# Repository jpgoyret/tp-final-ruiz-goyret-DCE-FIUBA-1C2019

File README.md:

# tp-final-ruiz-goyret-DCE-FIUBA-1C2019
Trabajo Práctico final de la materia Diseño de Circuitos Electrónicos en FIUBA - 1°C 2019

Integrantes del grupo:

  * Santiago Ruiz (98052)
  * Juan Pablo Goyret (99081)

## Resumen del trabajo práctico

El trabajo consiste en el diseño, simulación y armado en PCB de un amplificador de audio de potencia mayor a 40W. El tipo de amplificador diseñado es un clase H con etapa de salida en paralelo, realizando la conmutación propia de esta configuración mediante transistores MOSFET. Dada la necesidad de alimentar al amplificador clase H mediante dos valores distintos de tensión positiva y negativa, se diseñaron, por otra parte, dos fuente de switching de +12 y -12 V. 

## Descripción del repositorio

El repositorio de encuentra estructurado en 3 carpetas principales: 

- [Amplificador](https://github.com/jpgoyret/tp-final-ruiz-goyret-DCE-FIUBA-1C2019/tree/develop/Amplificador): documentación, simulaciones y proyecto en Kicad del amplificador.
- [Supply](https://github.com/jpgoyret/tp-final-ruiz-goyret-DCE-FIUBA-1C2019/tree/develop/Supply): documentación, simulaciones y proyecto en Kicad de las fuentes de switching.
- [DOC](https://github.com/jpgoyret/tp-final-ruiz-goyret-DCE-FIUBA-1C2019/tree/develop/DOC): referencias para el diseño de los circuitos, artículos útiles y hojas de datos de amplificadores comerciales que se usaron como referencia para el proyecto.

Cada subcarpeta cuenta con un archivo README.md propio describiendo su contenido y como debe ser analizado.

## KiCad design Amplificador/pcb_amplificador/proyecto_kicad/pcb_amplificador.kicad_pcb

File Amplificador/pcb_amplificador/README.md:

## Diseño del PCB del amplificador

En la carpeta [proyecto_kicad](./proyecto_kicad) se encuentran los archivos del proyecto en Kicad donde se diseñó el PCB del amplificador al mes de junio de 2019. Se incluyen las bibliotecas de componentes y "footprints" necesarios. Para visualizar correctamente el proyecto es suficiente con descargar la carpeta completa y ejecutar los archivos localizados allí adentro.

Por otra parte, en la carpeta [proyecto_kicad_actualizado](./proyecto_kicad_actualizado) se encuentra el proyecto de Kicad donde se han ido incluyendo las modificaciones hechas sobre el prototipo en un PCB rediseñado. El objetivo es que este sea una segunda resivisión del amplificador.

El diseño del PCB del amplificador fue realizado queriendo conservar el eje de simetría del amplificador con el fin facilitar su análisis. 

Los transistores de potencia que funcionan alimentados con +12V y -12V se encuentran colocados en la parte central de la placa, asociados a un mismo disipador (identificado por las líneas azules en el centro de placa en la captura que se observa más abajo) que el del multiplicador de Vbe para evitar un embalamiento térmico. Por otra parte, los transistores de potencia alimentados con +30V y -30V se situan  la derecha de la placa, asociados al disipador de mayores dimensiones. 

En entre unos y otros transistores de potencia se han colocado los conmutadores, cuyos transistores MOSFET son los integrados que se pueden observar en el PCB. A pesar de introducir mayores complejidades en el diseño del PCB, se han utilizado transistores MOSFET complementarios integrados con el fin de evitar distorsión por el hecho de que los NMOS y PMOS tuvieran distintas características e introdujeran asimetrías en el comportamiento de los conmutadores para el semiciclo positivo con respecto al negativo y viceversa.

La protección contra DC, incluyendo el relé, se encuentra a la derecha de los conmutadores y a la izquierda de los transistores de potencia que funcionan con +30V y -30V.

A la izquierda de la placa se encuentra el par diferencial, estando a su derecha la VAS.

En cuanto a los conectores, arriba a la izquierda se encuentra en puerto de audio de 3,5mm junto con con 3 pines para conectar un generador de funciones. En eje horizontal de placa y del lado izquierdo del disipador pequeño se encuentra una bornera utilizada para la conexión a tierra. Luego, sobre el eje vertical, arriba y abajo de la placa se encuentran las borneras de alimentación por las cuales ingresan +12V y +30V (arriba), y -12V y -30V (abajo). Finalmente, entre los transistores de potencia conectados a +30V y -30V se encuentra la bornera de salida de señal a el parlante. 

A continuación, de muestra una captura del PCB realizado en Kicad:

Y una vista 3D:

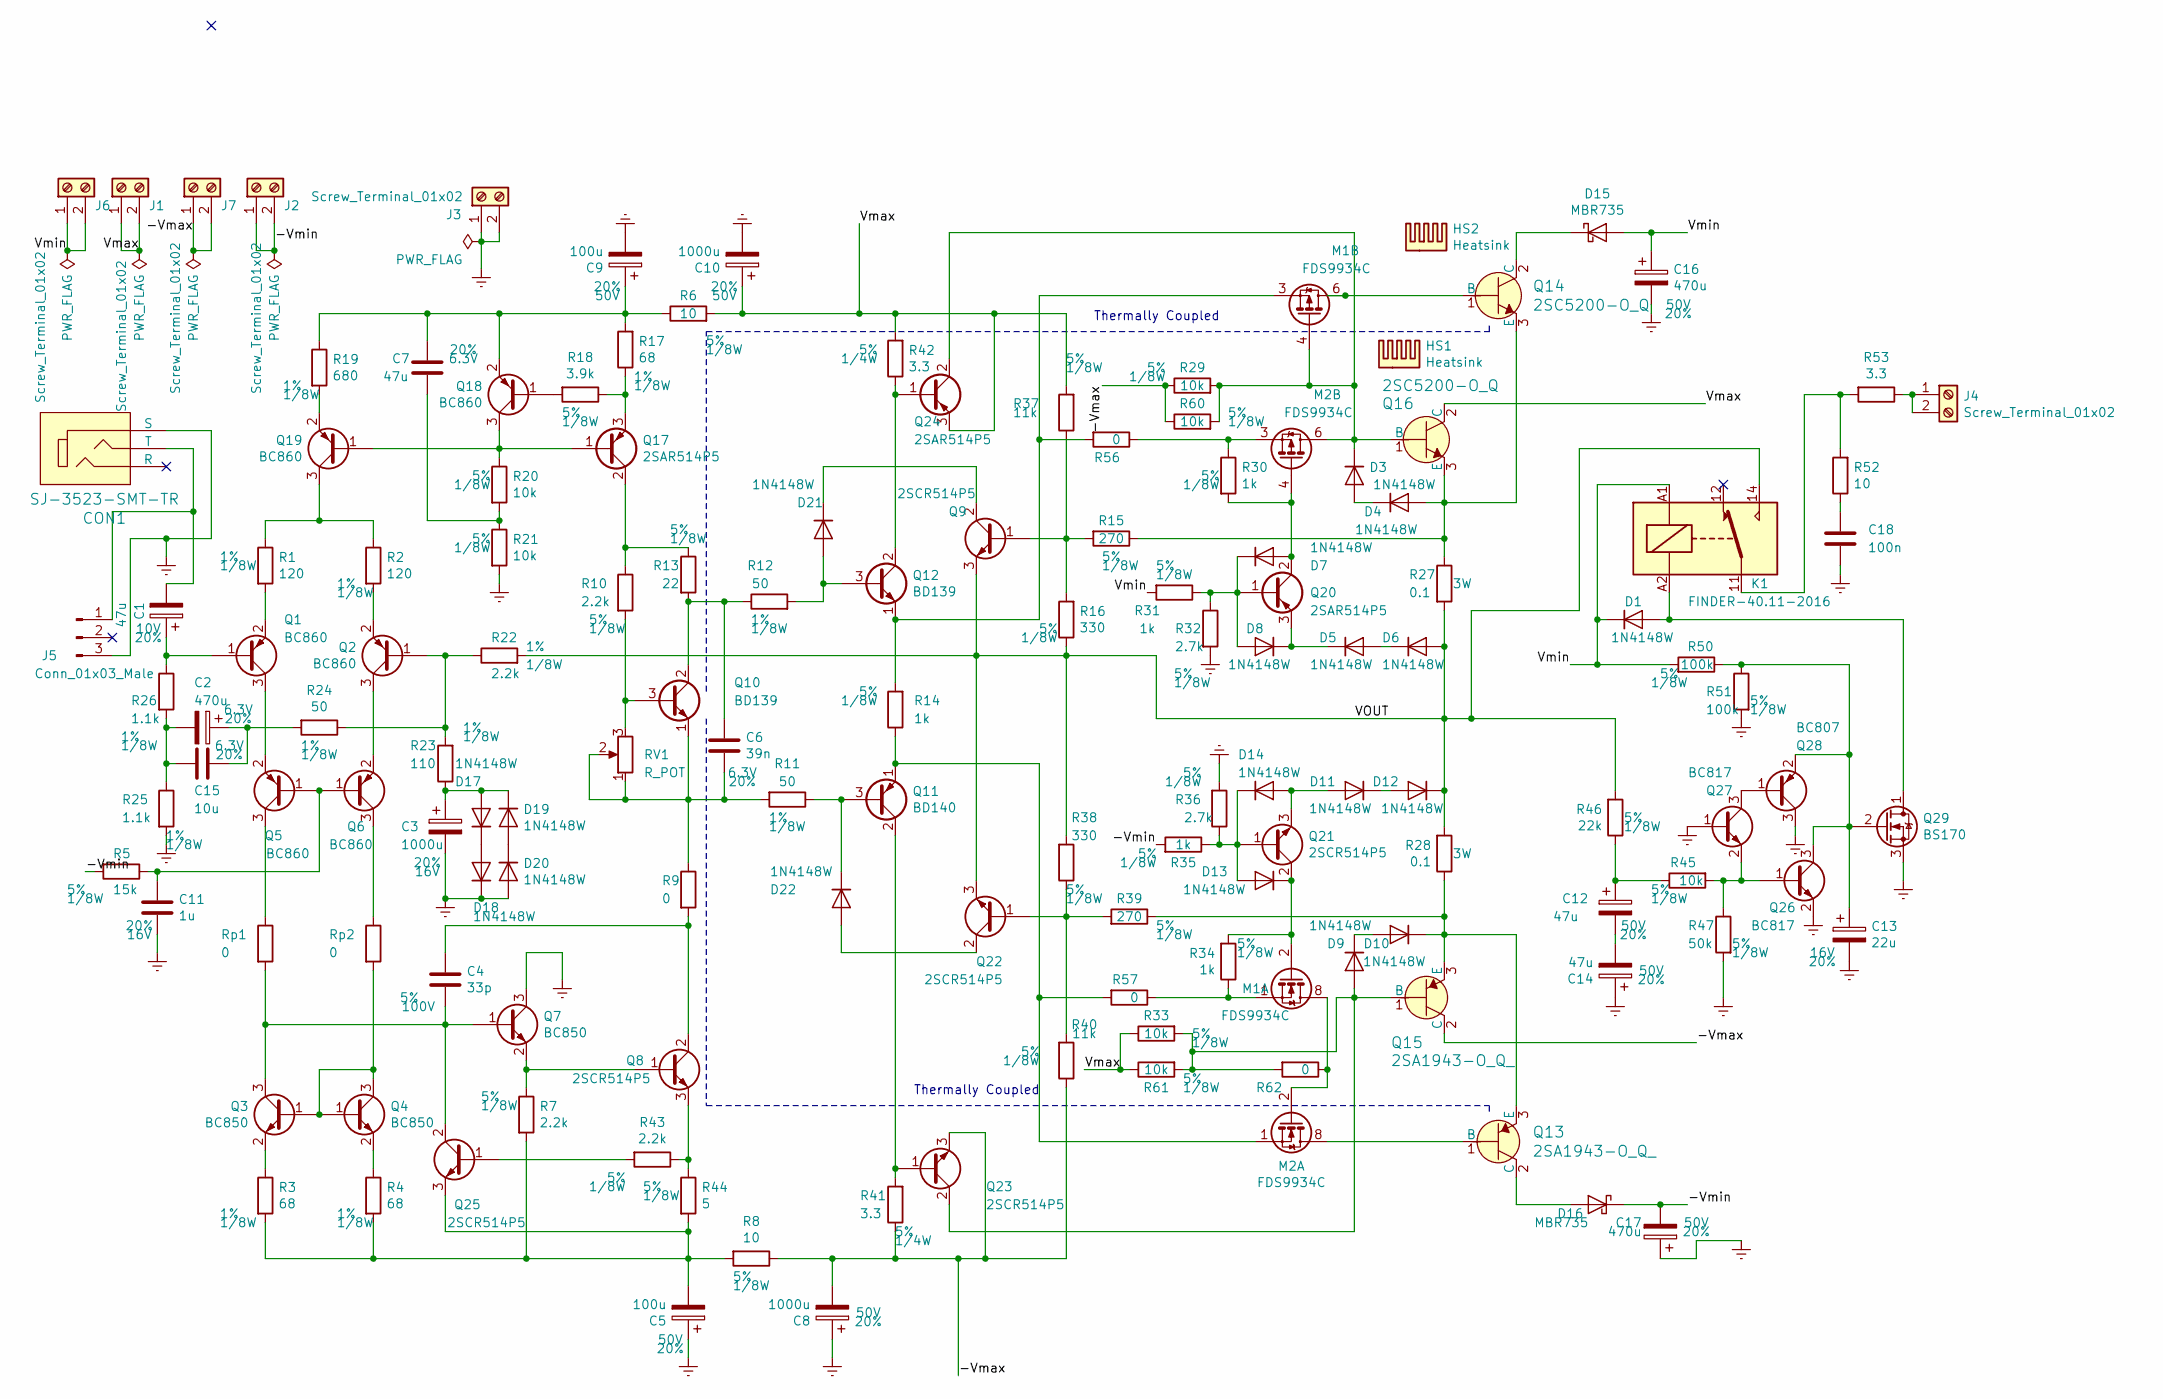
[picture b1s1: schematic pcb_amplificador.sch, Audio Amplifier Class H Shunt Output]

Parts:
C1: 47u; CP_Elec_5x5.4; Voltage 10V; Tolerance 20%
C2: 470u; CP_Elec_8x10.5; Voltage 6.3V; Tolerance 20%
C3: 1000u; CP_Elec_10x10.5; Voltage 16V; Tolerance 20%
C4: 33p; C_0805_2012Metric_Pad1.15x1.40mm_HandSolder; Tolerance 5%; Voltage 100V
C5, C9: 100u; CP_Elec_8x10.5; Voltage 50V; Tolerance 20%
C6: 39n; C_0805_2012Metric_Pad1.15x1.40mm_HandSolder; Voltage 6.3V; Tolerance 20%
C7: 47u; CP_Elec_6.3x5.4; Voltage 6.3V; Tolerance 20%
C8, C10: 1000u; CP_Radial_D12.5mm_P5.00mm; Voltage 50V; Tolerance 20%
C11: 1u; C_0805_2012Metric_Pad1.15x1.40mm_HandSolder; Tolerance 20%; Voltage 16V
C12, C14: 47u; CP_Elec_6.3x5.4; Voltage 50V; Tolerance 20%
C13: 22u; CP_Elec_5x5.4; Voltage 16V; Tolerance 20%
C15: 10u; C_0805_2012Metric_Pad1.15x1.40mm_HandSolder; Voltage 6.3V; Tolerance 20%
C16, C17: 470u; CP_Radial_D12.5mm_P5.00mm; Voltage 50V; Tolerance 20%
C18: 100n; C_Disc_D7.5mm_W5.0mm_P7.50mm
CON1: SJ-3523-SMT-TR; Switch_Slide_11.6x4mm_SJ-3523-SMT; MPN SJ-3523-SMT-TR; Digi-Key_PN CP-3523SJCT-ND
D1, D3, D4, D5, D6, D7, D8, D9, D10, D11, D12, D13, D14, D17, D18, D19, D20, D21, D22: 1N4148W; D_SOD-123
D15, D16: MBR735; TO-220-2_Vertical
HS1: Heatsink; disipador_1.8C
HS2: Heatsink; disipador_5.1C
J1, J2, J3, J4, J6, J7: Screw_Terminal_01x02; PhoenixContact_MCV_1,5_2-G-3.5_1x02_P3.50mm_Vertical
J5: Conn_01x03_Male; PinHeader_1x03_P2.54mm_Vertical
K1: FINDER-40.11-2016; Relay_SPDT_Schrack-RP-II-1-16A-FormC_RM5mm
M1, M2: FDS9934C; SOIC-8_3.9x4.9mm_P1.27mm
Q1, Q2, Q5, Q6, Q18, Q19: BC860; SOT-23_Handsoldering
Q3, Q4, Q7: BC850; SOT-23_Handsoldering
Q8, Q9, Q21, Q22, Q23, Q25: 2SCR514P5; SOT-89-3_Handsoldering
Q10, Q12: BD139; TO-126-3_Vertical
Q11: BD140; TO-126-3_Vertical
Q13, Q15: 2SA1943-O_Q_; TO-3P-5; MPN 2SA1943-O(Q); Digi-Key_PN 2SA1943-OQ-ND
Q14, Q16: 2SC5200-O_Q; TO-3P-5; MPN 2SC5200-O(Q); Digi-Key_PN 2SC5200-OQ-ND
Q17, Q20, Q24: 2SAR514P5; SOT-89-3_Handsoldering
Q26, Q27: BC817; SOT-23_Handsoldering
Q28: BC807; SOT-23_Handsoldering
Q29: BS170; TO-92_Inline
R1, R2: 120; R_0805_2012Metric_Pad1.15x1.40mm_HandSolder; Tolerance 1%
R3, R4, R17: 68; R_0805_2012Metric_Pad1.15x1.40mm_HandSolder; Tolerance 1%
R5: 15k; R_0805_2012Metric_Pad1.15x1.40mm_HandSolder; Tolerance 5%
R6, R8: 10; R_0805_2012Metric_Pad1.15x1.40mm_HandSolder; Tolerance 5%
R7, R10, R43: 2.2k; R_0805_2012Metric_Pad1.15x1.40mm_HandSolder; Tolerance 5%
R9, R56, R57, R62: 0; R_1206_3216Metric_Pad1.42x1.75mm_HandSolder
R11, R12, R24: 50; R_0805_2012Metric_Pad1.15x1.40mm_HandSolder; Tolerance 1%
R13: 22; R_0805_2012Metric_Pad1.15x1.40mm_HandSolder; Tolerance 5%
R14, R30, R31, R34, R35: 1k; R_0805_2012Metric_Pad1.15x1.40mm_HandSolder; Tolerance 5%
R15, R39: 270; R_0805_2012Metric_Pad1.15x1.40mm_HandSolder; Tolerance 5%
R16, R38: 330; R_0805_2012Metric_Pad1.15x1.40mm_HandSolder; Tolerance 5%
R18: 3.9k; R_0805_2012Metric_Pad1.15x1.40mm_HandSolder; Tolerance 5%
R19: 680; R_0805_2012Metric_Pad1.15x1.40mm_HandSolder; Tolerance 1%
R20, R21, R29, R33, R45, R60, R61: 10k; R_0805_2012Metric_Pad1.15x1.40mm_HandSolder; Tolerance 5%
R22: 2.2k; R_0805_2012Metric_Pad1.15x1.40mm_HandSolder; Tolerance 1%
R23: 110; R_0805_2012Metric_Pad1.15x1.40mm_HandSolder; Tolerance 1%
R25, R26: 1.1k; R_0805_2012Metric_Pad1.15x1.40mm_HandSolder; Tolerance 1%
R27, R28: 0.1; R_Axial_DIN0411_L9.9mm_D3.6mm_P12.70mm_Horizontal
R32, R36: 2.7k; R_0805_2012Metric_Pad1.15x1.40mm_HandSolder; Tolerance 5%
R37, R40: 11k; R_0805_2012Metric_Pad1.15x1.40mm_HandSolder; Tolerance 5%
R41, R42: 3.3; R_0805_2012Metric_Pad1.15x1.40mm_HandSolder; Tolerance 5%
R44: 5; R_0805_2012Metric_Pad1.15x1.40mm_HandSolder; Tolerance 5%
R46: 22k; R_0805_2012Metric_Pad1.15x1.40mm_HandSolder; Tolerance 5%
R47: 50k; R_0805_2012Metric_Pad1.15x1.40mm_HandSolder; Tolerance 5%
R50, R51: 100k; R_0805_2012Metric_Pad1.15x1.40mm_HandSolder; Tolerance 5%
R52: 10; R_Axial_DIN0614_L14.3mm_D5.7mm_P15.24mm_Horizontal
R53: 3.3; R_Axial_DIN0207_L6.3mm_D2.5mm_P7.62mm_Horizontal
RV1: R_POT; Potentiometer_Bourns_3314G_Vertical
Rp1, Rp2: 0; R_0805_2012Metric_Pad1.15x1.40mm_HandSolder

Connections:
/-Vmax: C8.2, J7.1, J7.2, Q15.2 (C), Q23.3 (E), R8.1, R29.1, R40.1, R41.1, R60.1
/-Vmin: C17.2, D16.1 (K), J2.1, J2.2, R5.2, R35.2
/VOUT: D6.2 (A), D12.1 (K), K1.14, Q9.3 (E), Q22.3 (E), R16.1, R22.2, R27.2, R28.2, R38.2, R46.2
/Vmax: C10.1, J1.1, J1.2, Q16.2 (C), Q24.3 (E), R6.2, R33.1, R37.2, R42.2, R61.1
/Vmin: C16.1, D1.1 (K), D15.2 (A), J6.1, J6.2, K1.A1, R31.2, R50.2
Earth: C3.2, C5.1, C8.1, C9.2, C10.2, C11.2, C13.2, C14.1, C16.2, C17.1, C18.1, CON1.1 (S), D18.1 (K), D20.2 (A), J3.1, J3.2, J5.3, Q7.3 (C), Q26.2 (E), Q27.1 (B), Q28.3 (C), Q29.3 (S), R21.2, R25.2, R32.2, R36.2, R47.2, R51.2
unnamed: C1.1, Q1.1 (B), R26.1
unnamed: C1.2, CON1.2 (T), J5.1
unnamed: C3.1, D17.2 (A), D19.1 (K), R23.1
unnamed: C4.1, Q8.2 (C), R9.2
unnamed: C4.2, Q3.3 (C), Q7.1 (B), Q25.2 (C), Rp1.2
unnamed: C5.2, Q25.3 (E), R3.2, R4.2, R7.2, R8.2, R44.2
unnamed: C6.1, Q10.1 (E), R9.1, R11.2, RV1.1, RV1.2
unnamed: C6.2, Q10.2 (C), R12.1, R13.2
unnamed: C7.1, R20.2, R21.1
unnamed: C7.2, C9.1, Q18.2 (E), R6.1, R17.2, R19.1
unnamed: C11.1, Q5.1 (B), Q6.1 (B), R5.1
unnamed: C12.1, R45.1, R46.1
unnamed: C12.2, C14.2
unnamed: C13.1, Q26.3 (C), Q28.2 (E), Q29.2 (G), R50.1, R51.1
unnamed: C2.1, C15.1, R24.2
unnamed: C2.2, C15.2, R25.1, R26.2
unnamed: C18.2, R52.1
unnamed: D1.2 (A), K1.A2, Q29.1 (D)
unnamed: D3.1 (K), M1.4 (G), M2.5 (D), M2.6 (D), Q16.1 (B), Q24.2 (C), R29.2, R60.2
unnamed: D3.2 (A), D4.1 (K)
unnamed: D4.2 (A), Q14.3 (E), Q16.3 (E), R15.1, R27.1
unnamed: D5.1 (K), D8.1 (K), Q20.3 (E)
unnamed: D5.2 (A), D6.1 (K)
unnamed: D7.1 (K), D8.2 (A), Q20.1 (B), R31.1, R32.1
unnamed: D7.2 (A), M2.4 (G), Q20.2 (C), R30.2
unnamed: D9.2 (A), Q15.1 (B), Q23.2 (C), R33.2, R61.2, R62.2
unnamed: D10.1 (K), Q13.3 (E), Q15.3 (E), R28.1, R39.1
unnamed: D9.1 (K), D10.2 (A)
unnamed: D11.1 (K), D12.2 (A)
unnamed: D11.2 (A), D14.2 (A), Q21.3 (E)
unnamed: D13.1 (K), M1.2 (G), Q21.2 (C), R34.2
unnamed: D13.2 (A), D14.1 (K), Q21.1 (B), R35.1, R36.1
unnamed: D15.1 (K), Q14.2 (C)
unnamed: D16.2 (A), Q13.2 (C)
unnamed: D17.1 (K), D18.2 (A)
unnamed: D19.2 (A), D20.1 (K)
unnamed: D21.1 (K), Q9.2 (C)
unnamed: D21.2 (A), Q12.3 (B), R12.2
unnamed: D22.1 (K), Q11.3 (B), R11.1
unnamed: D22.2 (A), Q22.2 (C)
unnamed: J4.1, J4.2, R53.1
unnamed: K1.11, R52.2, R53.2
unnamed: M1.1 (S), R34.1, R57.1
unnamed: M1.3 (1), Q12.1 (E), R14.2, R56.2
unnamed: M1.5 (D), M1.6 (D), Q14.1 (B)
unnamed: M1.7 (D), M1.8 (D), M2.2 (G), R62.1
unnamed: M2.1 (S), Q11.1 (E), R14.1, R57.2
unnamed: M2.3 (1), R30.1, R56.1
unnamed: M2.7 (D), M2.8 (D), Q13.1 (B)
unnamed: Q1.2 (E), R1.2
unnamed: Q1.3 (C), Q5.2 (E)
unnamed: Q2.1 (B), R22.1, R23.2, R24.1
unnamed: Q2.2 (E), R2.2
unnamed: Q2.3 (C), Q6.2 (E)
unnamed: Q3.1 (B), Q4.1 (B), Q4.3 (C), Rp2.2
unnamed: Q3.2 (E), R3.1
unnamed: Q4.2 (E), R4.1
unnamed: Q5.3 (C), Rp1.1
unnamed: Q6.3 (C), Rp2.1
unnamed: Q7.2 (E), Q8.1 (B), R7.1
unnamed: Q8.3 (E), R43.1, R44.1
unnamed: Q9.1 (B), R15.2, R16.2, R37.1
unnamed: Q10.3 (B), R10.2, RV1.3
unnamed: Q11.2 (C), Q23.1 (B), R41.2
unnamed: Q12.2 (C), Q24.1 (B), R42.1
unnamed: Q17.1 (B), Q18.3 (C), Q19.1 (B), R20.1
unnamed: Q17.2 (C), R10.1, R13.1
unnamed: Q17.3 (E), R17.1, R18.1
unnamed: Q18.1 (B), R18.2
unnamed: Q19.2 (E), R19.2
unnamed: Q19.3 (C), R1.1, R2.1
unnamed: Q22.1 (B), R38.1, R39.2, R40.2
unnamed: Q25.1 (B), R43.2
unnamed: Q26.1 (B), Q27.2 (E), R45.2, R47.1
unnamed: Q27.3 (C), Q28.1 (B)

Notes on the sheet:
Thermally Coupled

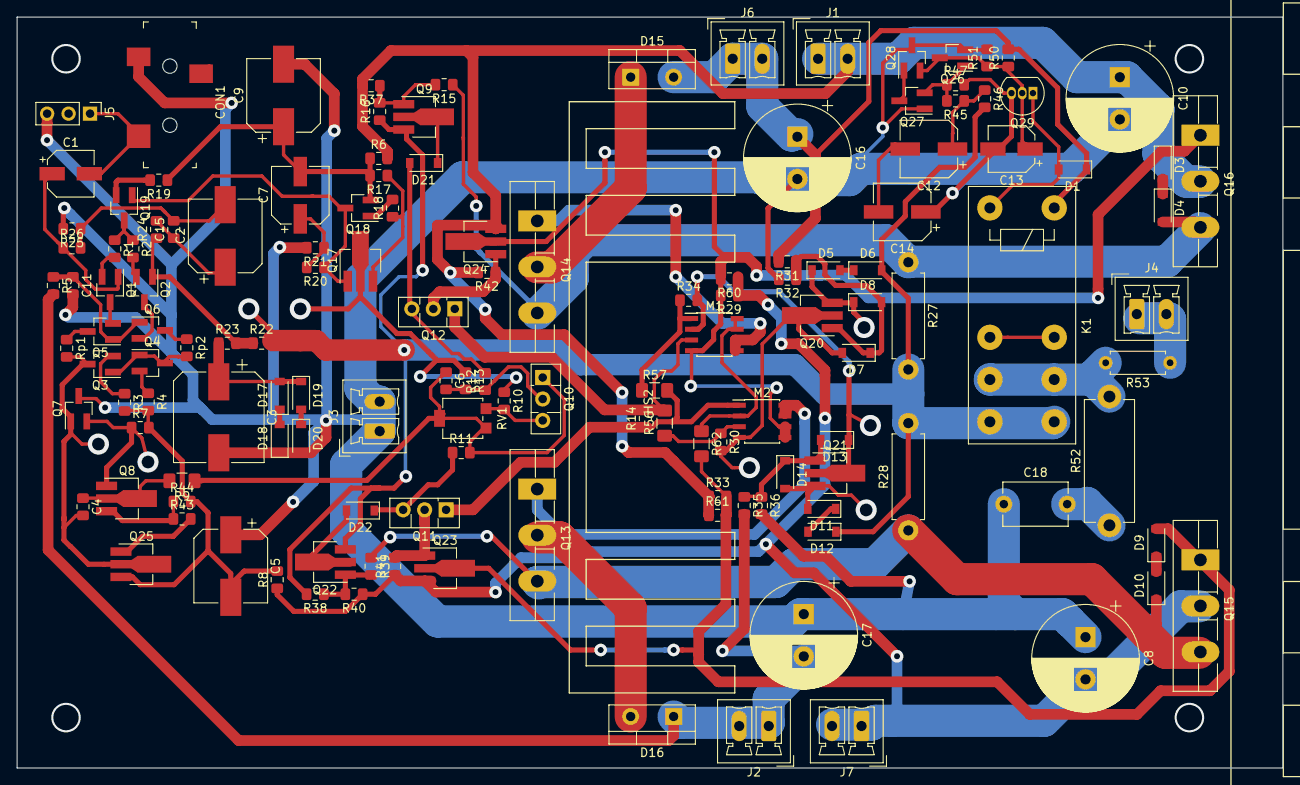
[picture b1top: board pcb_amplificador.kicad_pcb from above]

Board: 2 copper layers, 149.9 x 88.9 mm, 140 parts (0 on the bottom side), 81 nets.

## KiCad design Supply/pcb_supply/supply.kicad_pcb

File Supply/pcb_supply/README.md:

## Fuente de alimentación

En esta carpeta se encuentra el proyecto de diseño del PCB realizado en _KiCad_.
Se observa a continuación el esquemático circuital y el diseño final del PCB.

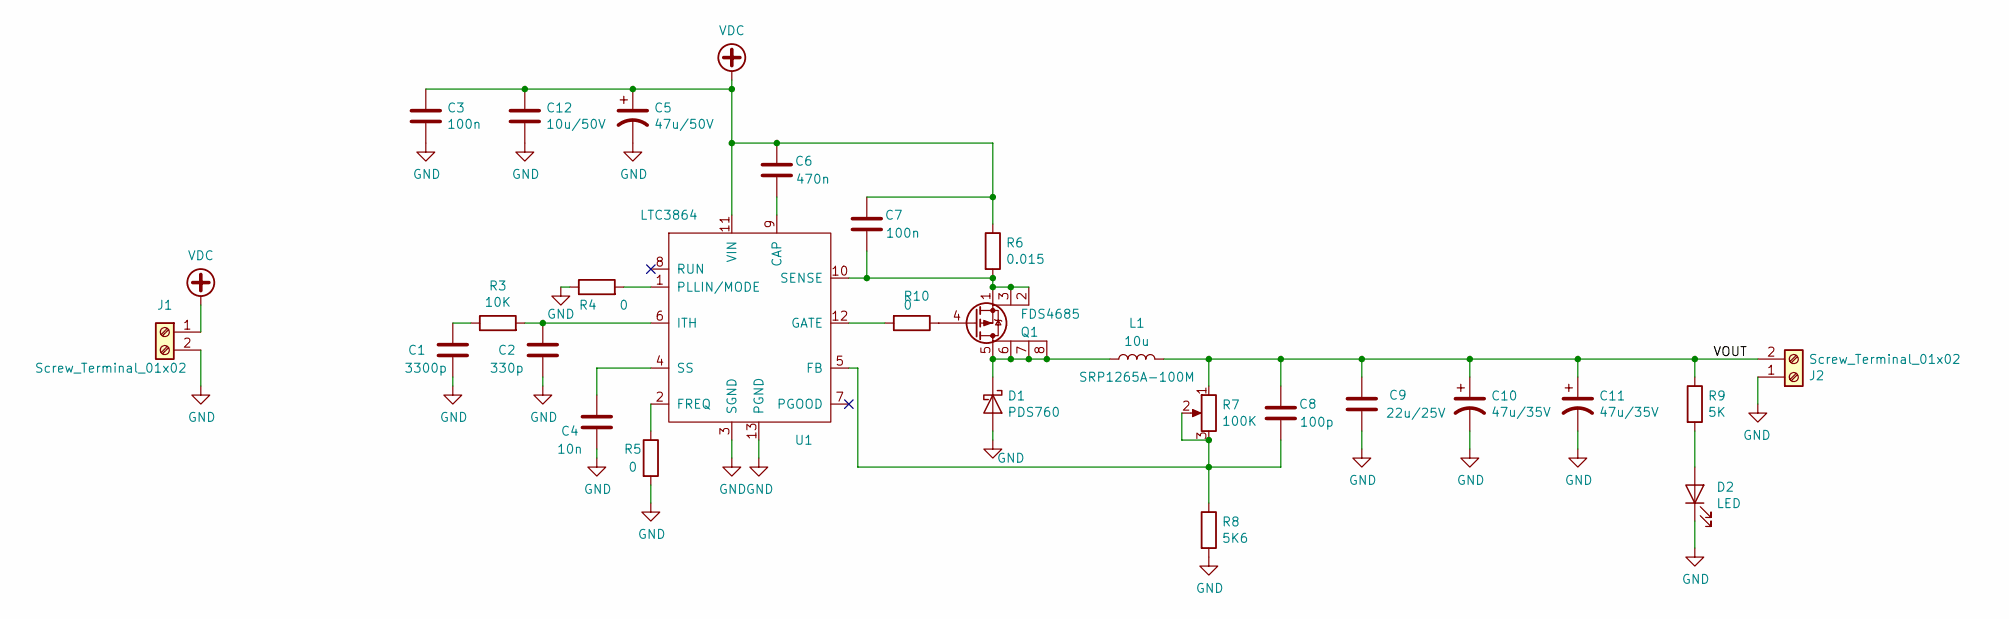
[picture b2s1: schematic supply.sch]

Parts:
C1: 3300p; C_0805_2012Metric
C2: 330p; C_0805_2012Metric
C3, C7: 100n; C_0805_2012Metric
C4: 10n; C_0805_2012Metric
C5: 47u/50V; CP_Elec_6.3x7.7
C6: 470n; C_0805_2012Metric
C8: 100p; C_0805_2012Metric
C9: 22u/25V; C_0805_2012Metric
C10, C11: 47u/35V; CP_Elec_6.3x5.8
C12: 10u/50V; C_0805_2012Metric
D1: PDS760; D_PowerDI-5
D2: LED; LED_0805_2012Metric
J1, J2: Screw_Terminal_01x02; 691102710002
L1: 10u; L_Bourns_SRP1245A
Q1: FDS4685; SOIC-8_3.9x4.9mm_P1.27mm
R3: 10K; R_0805_2012Metric
R4, R5, R10: 0; R_0805_2012Metric
R6: 0.015; R_2512_6332Metric
R7: 100K; Potentiometer_Bourns_3314J_Vertical
R8: 5K6; R_0805_2012Metric
R9: 5K; R_0805_2012Metric
U1: LTC3864; MSOP-12-1EP_3x4mm_P0.65mm_EP1.65x2.85mm

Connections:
/VOUT: C8.1, C9.1, C10.1, C11.1, J2.2, L1.2, R7.1, R9.1
GND: C1.2, C2.2, C3.2, C4.2, C5.2, C9.2, C10.2, C11.2, C12.2, D1.2 (A), D2.1 (K), J1.2, J2.1, R4.1, R5.2, R8.2, U1.3 (SGND), U1.13 (PGND)
unnamed: C1.1, R3.1
unnamed: C2.1, R3.2, U1.6 (ITH)
unnamed: C4.1, U1.4 (SS)
unnamed: C6.2, U1.9 (CAP)
unnamed: C7.2, Q1.1 (S), Q1.2 (S), Q1.3 (S), R6.2, U1.10 (SENSE)
unnamed: C8.2, R7.2, R7.3, R8.1, U1.5 (FB)
unnamed: D1.1 (K), L1.1, Q1.5 (D), Q1.6 (D), Q1.7 (D), Q1.8 (D)
unnamed: D2.2 (A), R9.2
unnamed: Q1.4 (G), R10.1
unnamed: R4.2, U1.1 (PLLIN/MODE)
unnamed: R5.1, U1.2 (FREQ)
unnamed: R10.2, U1.12 (GATE)
VDC: C3.1, C5.1, C6.1, C7.1, C12.1, J1.1, R6.1, U1.11 (VIN)

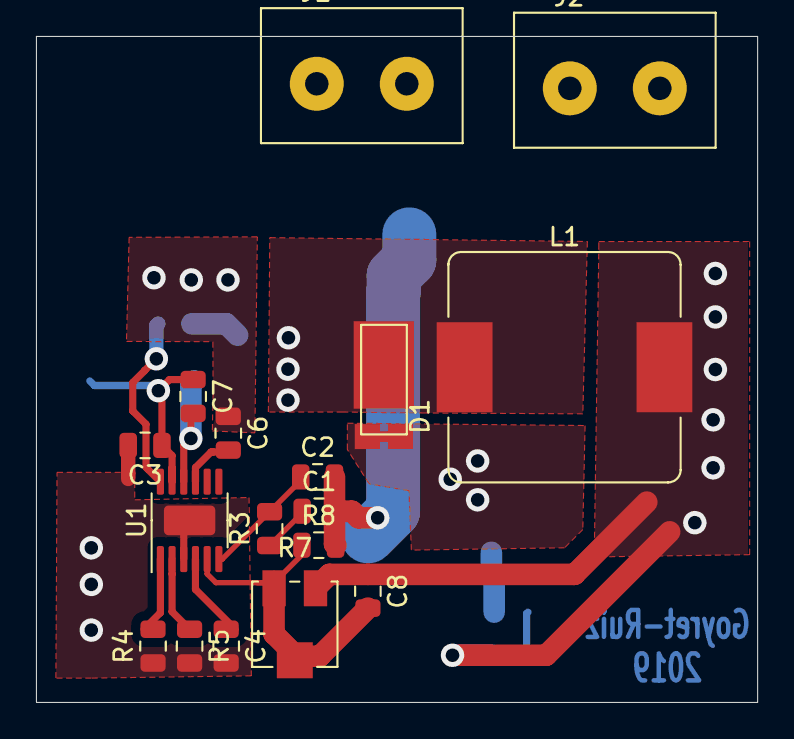
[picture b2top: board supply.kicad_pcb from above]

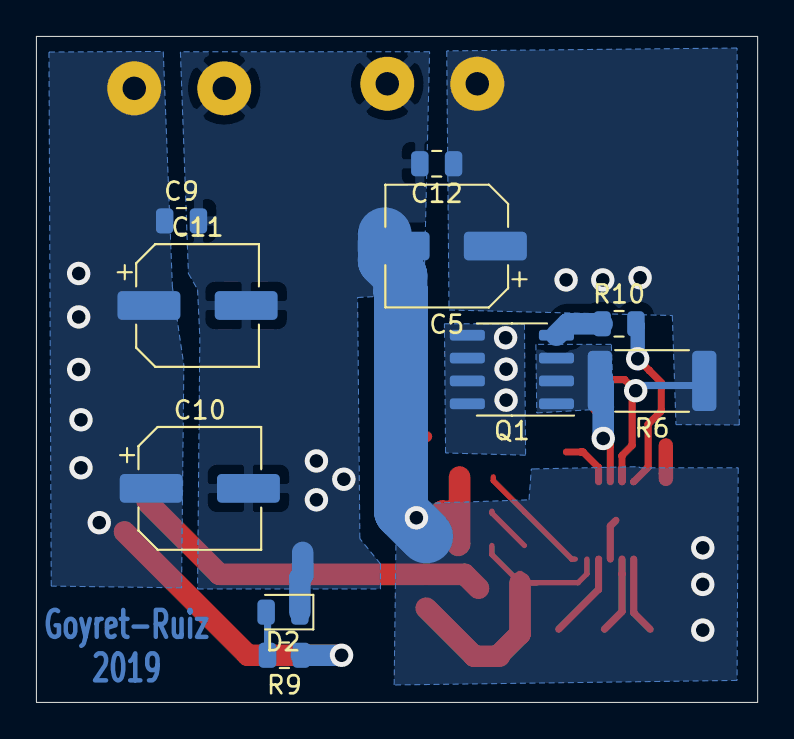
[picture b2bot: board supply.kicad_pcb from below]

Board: 2 copper layers, 40.1 x 37.0 mm, 27 parts (10 on the bottom side), 15 nets.

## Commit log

2019-05-19 Agregado de hojas de datos de amplificadores comerciales y documentos útiles sobre amplificadores G y H.
2019-05-19 Commit inicial develop. Lista TODO agregada
2019-05-19 Archivos ordenados en carpeta DOC
2019-05-19 Modificacon lista TODO
2019-05-20 Agregado de un boceto del amplificador elegido y sus especificaciones.
2019-05-20 Corrección de errores en el boceto
2019-05-23 Diseño fuente de alimentación
2019-05-23 TODO list actualizada
2019-05-23 Simulacion basica fuente switching subido
2019-05-24 Especificaciones fuente switching continuadas
2019-05-24 Especificaciones fuente corregidas
2019-05-24 Agregado de simulaciones del amplificador clase G (no terminado).
2019-05-26 Agregado de las simulación de las llaves de conmutación para la etapa de potencia en paralelo
2019-05-27 Correción sobre los comentarios en la simulación de la llave de conmutación.
2019-05-27 Correción sobre los comentarios en la simulación de la llave de conmutación(2).
2019-05-27 Agregado de simulación del THD del amplificador con etapa de salida en paralelo.
2019-05-27 Agregado de simulación del THD del amplificador con etapa de salida en paralelo.(2)
2019-05-27 Prueba de uso de MathJax para Markdown
2019-05-28 Actualizacion de las especificaciones (
2019-06-03 Actualización del circuito amplificador y sus especificaciones.
2019-06-05 Cambios en las especificaciones y en la llave de conmutación
2019-06-08 Actualización del circuito amplificador intregando protecciones por sobrecorriente y modificando la alimentación del par diferencial cascode para reducir la distorsión.
2019-06-11 Agregado de limitación de corriente para la VAS; cambio en la ubicación del potenciómetro en la VAS.
2019-06-11 Agregado del esquematico del amplificador (falta la protección contra tensión de DC en la salida)
2019-06-12 Agregado de la protección contra DC del amplificador en la simulación del LTSpice
2019-06-12 Actualizacion del esquematico del amplificador
2019-06-13 Actualizacion del esquematico del amplificador(2)
2019-06-15 Comienzo del diseño del PCB del amplificador
2019-06-15 Avance con el PCB
2019-06-15 Avance con el PCB (2)
2019-06-18 Avance PCB
2019-06-20 Modificacion del modelo de los transistores de salida y cambios a algunos capacitores de filtrado del circuito; actualización de las especificaciones y agregado de diagramas.
2019-06-20 Modificacion del modelo de los transistores de salida y cambios a algunos capacitores de filtrado del circuito; actualización de las especificaciones y agregado de diagramas.(2)
2019-06-20 Modificacion del modelo de los transistores de salida y cambios a algunos capacitores de filtrado del circuito; actualización de las especificaciones y agregado de diagramas.(3)
2019-06-20 PCB y simulación de fuente switching
2019-06-22 Cambios en el esquematico del PCB
2019-06-25 Primer diseño completo de todo el PCB del amplificador
2019-06-25 Actualización de la documentación
2019-06-26 Actualización de la documentación (2)
2019-06-27 Actualizacion documentacion supply
2019-06-28 PCB y especificaciones supply actualizado
2019-06-28 Supply resultados simulacion
2019-06-29 Emprolijado directorio PCB
2019-07-02 PCB supply arreglos menores
2019-07-05 Se mueve el contenido sobre PCB de la rama PCB_review a develop
2019-07-05 Cambios en la documentación en la carpeta del amplificador y en DOC
2019-07-05 Cambio documentacion Supply
2019-07-05 Cambios menores documentacion
2019-07-05 Imagenes sim resubidas
2019-07-06 Agregado de imagenes de las mediciones del 5/7/19 y descripción de las medciciones realizadas sobre el amplificador
2019-07-06 Agregado de imagenes de las mediciones del 5/7/19 y descripción de las medciciones realizadas sobre el amplificador(2)
2019-07-11 Agregado de las mediciones del día 10/7/19
2019-07-15 Agregado de las mediciones realizadas el 12/7/19 sobre el amplificador
2019-07-21 Agregado de las mediciones realizadas en el día 19/7/19
2019-07-26 Actualización de las especificaciones del amplificador
2019-07-26 Nuevos cambios en las especificaciones y ampliación de la documentación del amplificador
2019-07-26 Mediciones supply agregadas
2019-07-31 Correcciones en la documentación del amplificador y agregado de boceto de la justificación de los valoresde los componentes
2019-08-01 Cambios varios en la documentación del amplificador; agregado de ecuaciones en latex y gráficos al archivo que explica como se hallaron los valores de los componentes; agregado de documento que expli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
2019-08-01 Cambios varios en la documentación del amplificador; agregado de ecuaciones en latex y gráficos al archivo que explica como se hallaron los valores de los componentes; agregado de documento que expli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
2019-08-01 Cambios varios en la documentación del amplificador; agregado de ecuaciones en latex y gráficos al archivo que explica como se hallaron los valores de los componentes; agregado de documento que expli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
2019-08-01 Cambios varios en la documentación del amplificador; agregado de ecuaciones en latex y gráficos al archivo que explica como se hallaron los valores de los componentes; agregado de documento que expli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
2019-08-02 Prueba acceso archivos ruta relativa
2019-08-02 Arreglos menores rutas
2019-08-02 Arreglos menores rutas (2)
2019-08-13 Agregado de datos extra de los componentes en el esquemático del amplificador y cambios menores
2019-08-15 Agregado de la caracterización de los limitadores contra sobrecorriente
2019-08-15 Agregado de la caracterización de los limitadores contra sobrecorriente(2)
2019-08-27 Agregado de los resultados de la medicion de la proteccion de DC
2019-08-28 Agregado de los resultados de la medicion de la proteccion de DC (2). Agregado de simulaciones de la protección de DC
2019-09-07 Agregado de los resultados de las mediciones de THD con las protecciones y desarrollo de la explicación del comportamiento de los limitadores de corriente en el semicilo negativo
2019-09-07 Agregado de los resultados de las mediciones de THD con las protecciones y desarrollo de la explicación del comportamiento de los limitadores de corriente en el semicilo negativo(2)
2019-09-24 Revision PCB supply
2019-09-24 Comienzo con la 3ra revisión de la fuente de switching
2019-09-25 Comienzo con la 3ra revisión de la fuente de switching(2)
2019-09-25 Comienzo con la 3ra revisión de la fuente de switching(3)
2019-10-27 Prueba PushPull supply
2019-11-05 Agregado de conexión Kelvin a la fuente de switching rediseñada
2019-11-13 2da version de la placa de la fuente de switching para mandar a hacer
2019-12-08 Agregado tabla comparativa especificaiones
2019-12-08 Correcciones menores
2019-12-08 Agregado valores diseno y simulado
2019-12-10 Agregado de las mediciones finales y algunos cambios menores
2019-12-10 Prueba de gitignore
2019-12-10 Prueba de gitignore (2)
2019-12-11 Agregado informacion supply
2019-12-11 Agregado informacion simulacion supply
2019-12-11 Agregado mediciones supply
2019-12-11 Corecciones menores supply
2019-12-11 Agregado de las mediciones de eficiencia de amplificador y de mediciones de la fuente de switching
2019-12-11 Agregado de las mediciones de eficiencia de amplificador y de mediciones de la fuente de switching(2)
2019-12-11 Cambios menores
2019-12-12 Agregado medicion PSNR
2019-12-13 Agregado del grafico de la eficiencia
2019-12-19 Agregado mediciones dia de evaluacion
2019-12-19 Agregado imagenes supply
2019-12-20 Cambios menores (2)
